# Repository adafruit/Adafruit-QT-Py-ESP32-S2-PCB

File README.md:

## Adafruit QT Py ESP32-S2 WiFi Dev Board with STEMMA QT PCB

<a href="http://www.adafruit.com/products/5325"><br/>
Click here to purchase one from the Adafruit shop</a>

PCB files for the Adafruit QT Py ESP32-S2 WiFi Dev Board with STEMMA QT. 

Format is EagleCAD schematic and board layout
* https://www.adafruit.com/product/5325

### Description

What has your favorite Espressif WiFi microcontroller, comes with our favorite connector - the STEMMA QT, a chainable I2C port, and has lots of Flash and RAM memory for your next IoT project? What will make your next IoT project flyyyyy? What a cutie pie! Or is it... a QT Py? This diminutive dev board comes with one of our new favorite lil chips, the ESP32-S2! 

The ESP32-S2 is a highly-integrated, low-power, 2.4 GHz Wi-Fi System-on-Chip (SoC) solution that now has built-in native USB as well as some other interesting new technologies like Time of Flight distance measurements. With its state-of-the-art power and RF performance, this SoC is an ideal choice for a wide variety of application scenarios relating to the Internet of Things (IoT), wearable electronics, and smart homes.

Please note the QT Py ESP32-S2 has a single-core 240 MHz chip, so it won't be as fast as ESP32's with dual-core. Also, there is no Bluetooth support. However, we are super excited about the ESP32-S2's native USB which unlocks a lot of capabilities for advanced interfacing! This ESP32-S2 mini-module we are using on the QT Py comes with 4 MB flash and 2 MB PSRAM so you can buffer massive JSON files for parsing!

OLEDs! Inertial Measurement Units! Sensors a-plenty. All plug-and-play thanks to the innovative chainable design: SparkFun Qwiic-compatible STEMMA QT connectors for the I2C bus so you don't even need to solder! Just plug in a compatible cable and attach it to your MCU of choice, and you’re ready to load up some software and measure some light. Seeed Grove I2C boards will also work with this adapter cable.

Pinout and shape are Seeed Xiao compatible, with castellated pads so you can solder it flat to a PCB. In addition to the QT connector, we also added an RGB NeoPixel (with controllable power pin to allow for ultra-low-power usage), a reset button (great for restarting your program or entering the bootloader) and a button on GPIO 0 for entering the ROM bootloader or for user input

Runs Arduino like a dream, and CircuitPython projects are fantastically fun.

### License

Adafruit invests time and resources providing this open source design, please support Adafruit and open-source hardware by purchasing products from [Adafruit](https://www.adafruit.com)!

Designed by Limor Fried/Ladyada for Adafruit Industries.

Creative Commons Attribution/Share-Alike, all text above must be included in any redistribution. 
See license.txt for additional details.

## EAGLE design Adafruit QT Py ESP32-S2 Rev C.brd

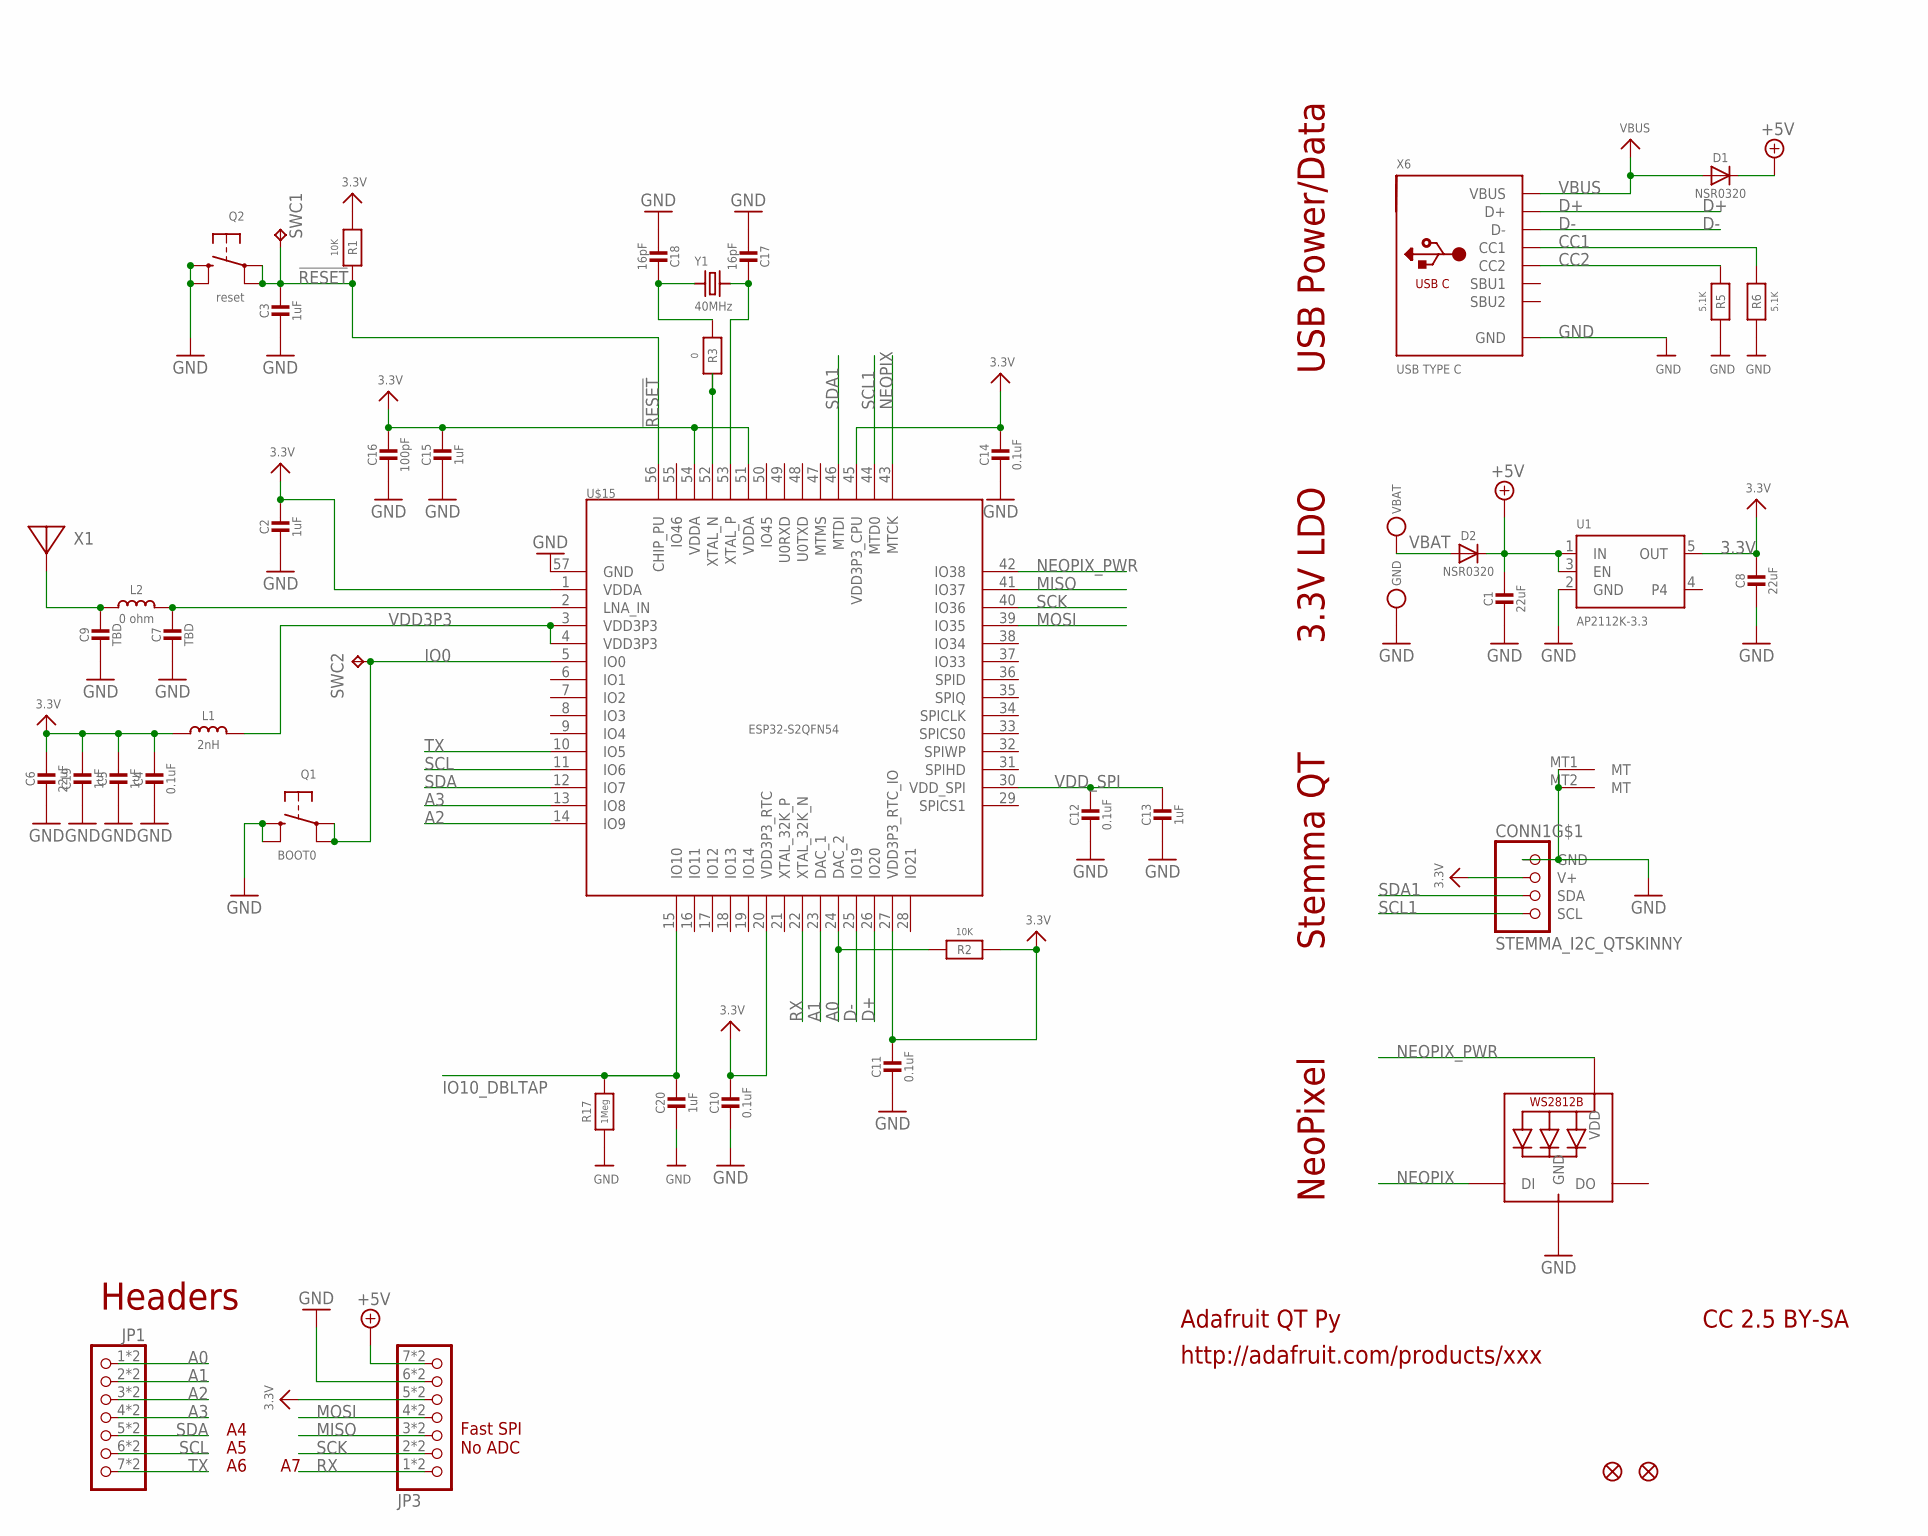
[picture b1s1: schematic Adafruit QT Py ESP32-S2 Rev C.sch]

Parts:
C1, C6, C8: 22uF; 0805-NO
C2, C3, C5, C13, C15, C19, C20: 1uF; _0402NO
C4, C10, C11, C12, C14: 0.1uF; _0402NO
C7, C9: TBD; _0402NO
C16: 100pF; _0402NO
C17, C18: 16pF; _0402NO
CONN1: STEMMA_I2C_QTSKINNY; JST_SH4_SKINNY
D1, D2: NSR0320; SOD-323_MINI
GND: TESTPOINT_MINUS; TESTPOINT_MINUS_1X3MM
JP1, JP3: HEADER-1X7_CASTEL; 1X07_CASTEL
L1: 2nH; _0402
L2: 0 ohm; _0402
LED1: WS2812B_SK6805_1515; SK6805_1515
Q1: BOOT0; BTN_KMR2_4.6X2.8
Q2: reset; BTN_KMR2_4.6X2.8
R1, R2: 10K; _0402NO
R3: 0; _0402NO
R5, R6: 5.1K; _0402NO
R17: 1Meg; _0402NO
SWC1, SWC2: TPB1,27; B1,27
U1: AP2112K-3.3; SOT23-5
U$6, U$8: FIDUCIAL_1MM
U$15: ESP32-S2QFN54; QFN56_7X7
VBAT: TESTPOINT_PLUS13; TESTPOINT_PLUS_1X3MM
X1: ANTENNA_JOHANSON_2450AT18B100; ANT_2450AT18B100
X6: USB TYPE C; USB_C_CUSB31-CFM2AX-01-X
Y1: 40MHz; CRYSTAL_2X1.6

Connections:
3.3V: C2.1, C4.1, C5.1, C6.1, C8.1, C10.1, C11.1, C14.1, C15.1, C16.1, C19.1, CONN1.2 (V+), JP3.5, JP3.5C (5), L1.1, R1.1, R2.1, U1.5 (OUT), U$15.1 (VDDA), U$15.20 (VDD3P3_RTC), U$15.27 (VDD3P3_RTC_IO), U$15.45 (VDD3P3_CPU), U$15.51 (VDDA), U$15.54 (VDDA)
!RESET: C3.1, Q2.A, Q2.A' (P1), R1.2, SWC1.TP, U$15.56 (CHIP_PU)
+5V: C1.1, D1.C, D2.C, JP3.7, JP3.7C (7), U1.1 (IN), U1.3 (EN)
A0: JP1.1, JP1.1C (1), R2.2, U$15.24 (DAC_2)
A1: JP1.2, JP1.2C (2), U$15.23 (DAC_1)
A2: JP1.3, JP1.3C (3), U$15.14 (IO9)
A3: JP1.4, JP1.4C (4), U$15.13 (IO8)
CC1: R6.2, X6.A5 (CC1)
CC2: R5.2, X6.B5 (CC2)
D+: U$15.26 (IO20), X6.A6 (D+), X6.B6 (D+)
D-: U$15.25 (IO19), X6.A7 (D-), X6.B7 (D-)
GND: C1.2, C2.2, C3.2, C4.2, C5.2, C6.2, C7.2, C8.2, C9.2, C10.2, C11.2, C12.2, C13.2, C14.2, C15.2, C16.2, C17.2, C18.2, C19.2, C20.2, CONN1.1 (GND), CONN1.MT1 (MT), CONN1.MT2 (MT), GND.P$1, JP3.6, JP3.6C (6), LED1.4 (GND), Q1.B (S), Q1.B' (S1), Q2.B (S), Q2.B' (S1), R5.1, R6.1, R17.1, U1.2 (GND), U$15.57 (GND), X6.A1B12 (GND), X6.B1A12 (GND)
IO0: Q1.A, Q1.A' (P1), SWC2.TP, U$15.5 (IO0)
IO10_DBLTAP: C20.1, R17.2, U$15.15 (IO10)
MISO: JP3.3, JP3.3C (3), U$15.41 (IO37)
MOSI: JP3.4, JP3.4C (4), U$15.39 (IO35)
unnamed: C7.1, L2.2, U$15.2 (LNA_IN)
unnamed: C9.1, L2.1, X1.FP
unnamed: R3.2, U$15.52 (XTAL_N)
unnamed: C17.1, U$15.53 (XTAL_P), Y1.3 (2)
unnamed: C18.1, R3.1, Y1.1
NEOPIX: LED1.1 (DI), U$15.43 (MTCK)
NEOPIX_PWR: LED1.2 (VDD), U$15.42 (IO38)
RX: JP3.1, JP3.1C (1), U$15.22 (XTAL_32K_N)
SCK: JP3.2, JP3.2C (2), U$15.40 (IO36)
SCL: JP1.6, JP1.6C (6), U$15.11 (IO6)
SCL1: CONN1.4 (SCL), U$15.44 (MTD0)
SDA: JP1.5, JP1.5C (5), U$15.12 (IO7)
SDA1: CONN1.3 (SDA), U$15.46 (MTDI)
TX: JP1.7, JP1.7C (7), U$15.10 (IO5)
VBAT: D2.A, VBAT.P$1
VBUS: D1.A, X6.A4B9 (VBUS), X6.B4A9 (VBUS)
VDD3P3: L1.2, U$15.3 (VDD3P3), U$15.4 (VDD3P3)
VDD_SPI: C12.1, C13.1, U$15.30 (VDD_SPI)

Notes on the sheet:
Adafruit QT Py
http://adafruit.com/products/xxx
CC 2.5 BY-SA
NeoPixel
Stemma QT
3.3V LDO
USB Power/Data
Headers
Fast SPI No ADC

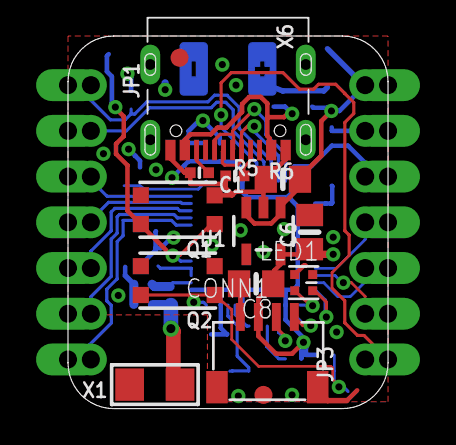
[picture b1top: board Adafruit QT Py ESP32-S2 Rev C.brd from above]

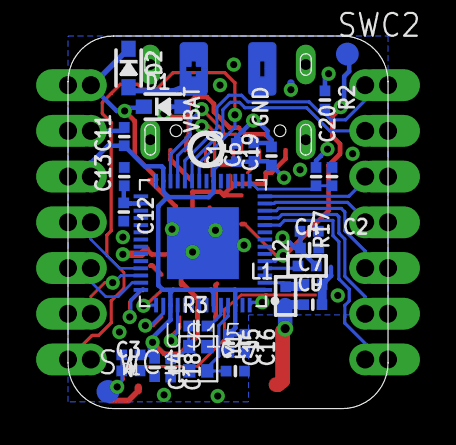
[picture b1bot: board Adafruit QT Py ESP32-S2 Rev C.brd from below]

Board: 4 copper layers, 17.8 x 20.7 mm, 50 parts (33 on the bottom side), 34 nets.

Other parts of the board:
U$7: QTPYS2_BOT
U$12: PCBFEAT-REV-040
U$13: QTPY_ESP32_TOP

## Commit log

2021-12-21 Added PCB files
2021-12-21 Add PrettyPins
2021-12-22 Add factory reset file.
2022-01-04 Update file name.
2022-01-13 Add uFL board files.
2022-03-29 Add latest board files.

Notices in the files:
parts and their libraries:
microbuilder: This work is placed in the public domain, and may be freely used for commercial and non-commercial work with the following conditions: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
